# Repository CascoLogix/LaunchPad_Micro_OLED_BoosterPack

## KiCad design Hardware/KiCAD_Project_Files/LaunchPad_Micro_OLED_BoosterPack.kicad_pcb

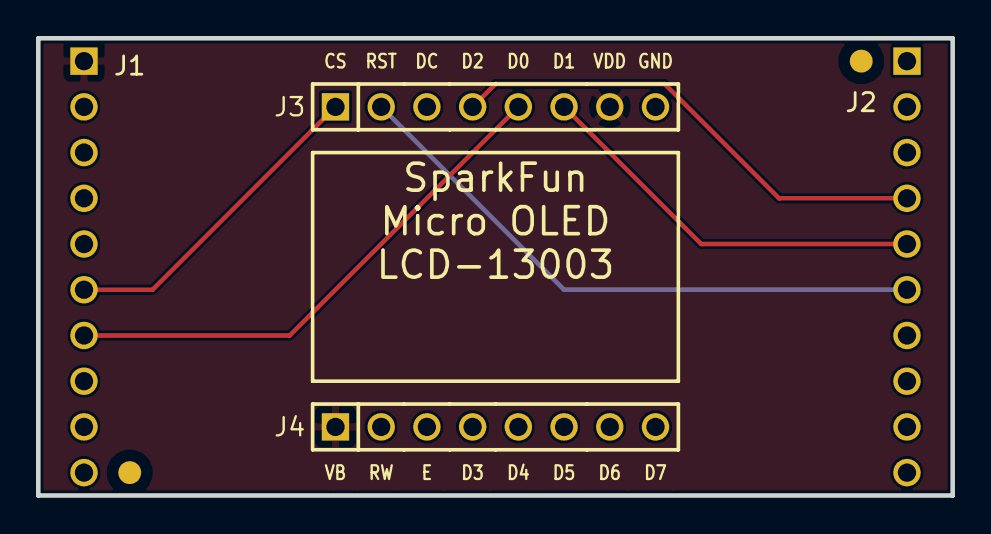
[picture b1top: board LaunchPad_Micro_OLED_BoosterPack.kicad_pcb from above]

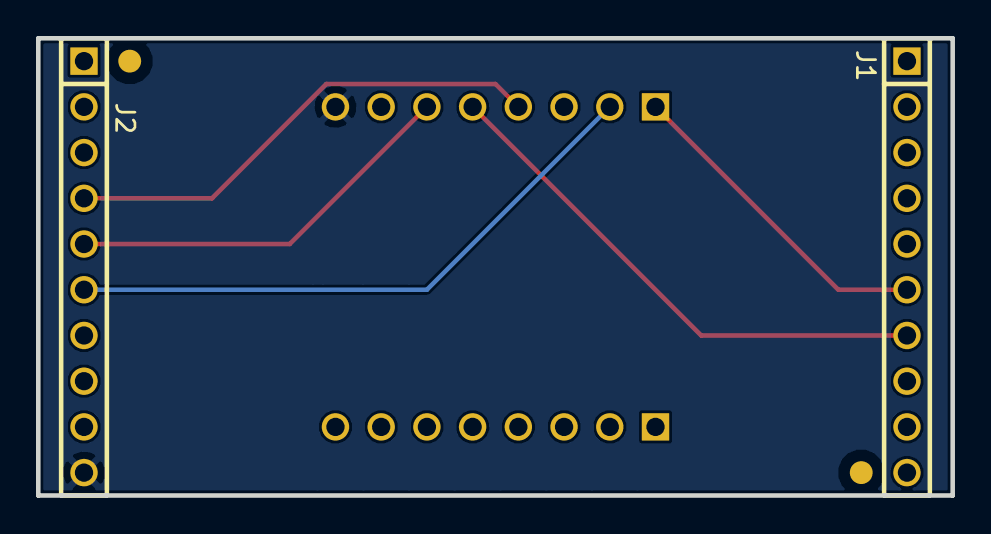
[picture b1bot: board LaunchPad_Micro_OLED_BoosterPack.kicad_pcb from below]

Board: 2 copper layers, 50.8 x 25.4 mm, 4 parts (2 on the bottom side), 7 nets.

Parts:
J1, J2: 1x10-PIN HEADER; HEADER_100MIL_1R10P_PTH
J3, J4: 1x8-PIN HEADER; HEADER_M_2.54MM_1R8P_ST_AU_PTH

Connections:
/3V3: J1.1, J3.7, J4.1
/CS: J1.6, J3.1
/D0/SCK: J1.7, J3.5
/D1/SDI: J2.5, J3.6
/D2/SDO: J2.4, J3.4
/GND: J2.10, J3.8
/RESET: J2.6, J3.2

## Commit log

2015-04-12 First commit.
